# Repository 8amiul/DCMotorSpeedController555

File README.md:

# DCMotorSpeedController555

It was my first attempt to design a PCB on KiCad.

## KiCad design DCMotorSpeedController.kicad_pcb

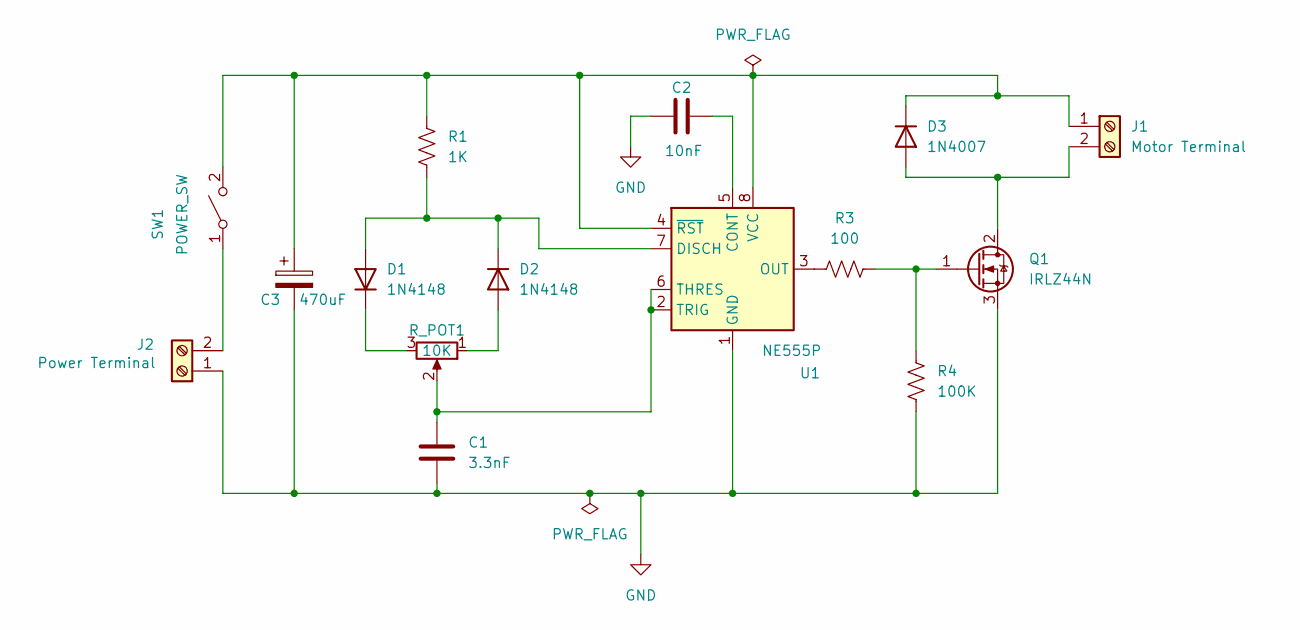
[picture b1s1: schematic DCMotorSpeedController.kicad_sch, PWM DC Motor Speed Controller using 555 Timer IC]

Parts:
C1: 3.3nF; C_Disc_D4.7mm_W2.5mm_P5.00mm
C2: 10nF; C_Disc_D4.7mm_W2.5mm_P5.00mm
C3: 470uF; CP_Radial_D10.0mm_P5.00mm
D1, D2: 1N4148; D_DO-35_SOD27_P7.62mm_Horizontal
D3: 1N4007; D_DO-41_SOD81_P10.16mm_Horizontal
J1: Motor Terminal; TerminalBlock_MaiXu_MX126-5.0-02P_1x02_P5.00mm
J2: Power Terminal; TerminalBlock_MaiXu_MX126-5.0-02P_1x02_P5.00mm
Q1: IRLZ44N; TO-220-3_Vertical
R1: 1K; R_Axial_DIN0204_L3.6mm_D1.6mm_P7.62mm_Horizontal
R3: 100; R_Axial_DIN0204_L3.6mm_D1.6mm_P7.62mm_Horizontal
R4: 100K; R_Axial_DIN0204_L3.6mm_D1.6mm_P7.62mm_Horizontal
R_POT1: 10K; Potentiometer_Alps_RK163_Single_Horizontal
SW1: POWER_SW; SW_Slide_SPDT_Straight_CK_OS102011MS2Q
U1: NE555P; DIP-8_W7.62mm

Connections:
GND: C1.2, C2.1, C3.2, J2.1, Q1.3 (S), R4.1, U1.1 (GND)
unnamed: D1.2 (A), D2.1 (K), R1.2, U1.7 (DISCH)
unnamed: D1.1 (K), R_POT1.3
unnamed: D2.2 (A), R_POT1.1
unnamed: D3.2 (A), J1.2, Q1.2 (D)
unnamed: C3.1, D3.1 (K), J1.1, R1.1, SW1.2 (B), U1.4 (~RST), U1.8 (VCC)
unnamed: J2.2, SW1.1 (A)
unnamed: Q1.1 (G), R3.2, R4.2
unnamed: C2.2, U1.5 (CONT)
unnamed: R3.1, U1.3 (OUT)
unnamed: C1.1, R_POT1.2, U1.2 (TRIG), U1.6 (THRES)

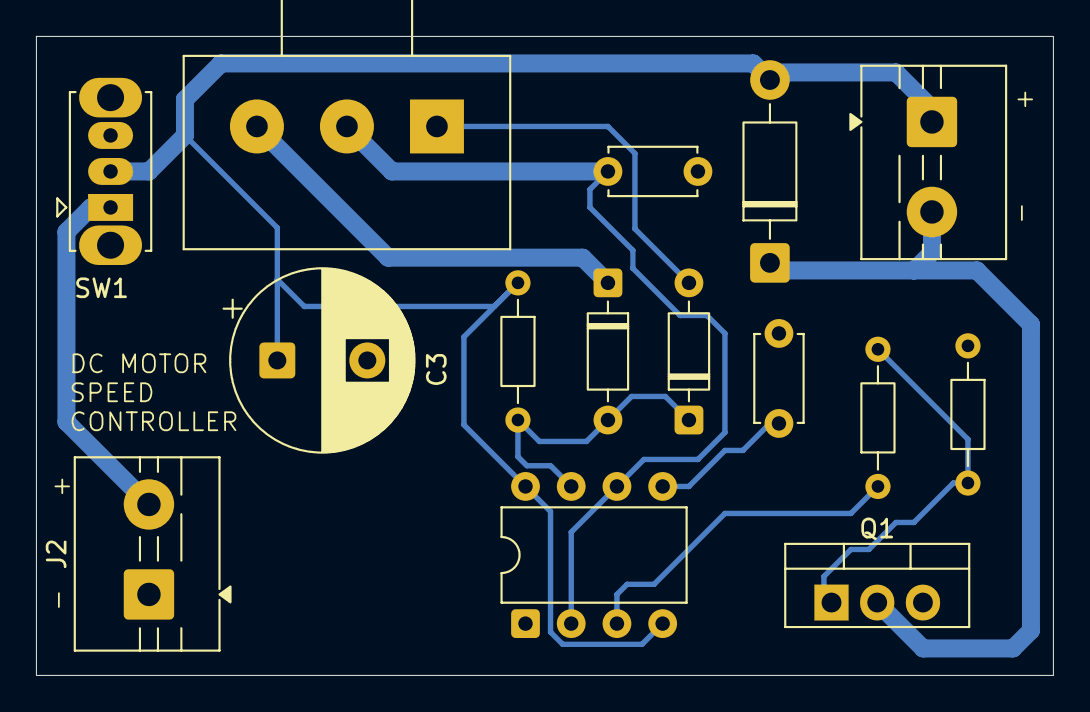
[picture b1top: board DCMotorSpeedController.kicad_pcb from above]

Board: 2 copper layers, 56.5 x 35.5 mm, 15 parts (0 on the bottom side), 11 nets.
